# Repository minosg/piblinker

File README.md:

# PiBlinker

A simple python library that provides easy access to to GPIO ports of 20, 21, 26
and enables user to debug behavior on a raspberry pi2 using an RGB led.

It also allows you to attach an ATTINY85 programmed as slave,
if you wish to have external ADC readouts in your project.

Hardware schematics for a simple shield are included, and it costs around 5$ to
manufacture using collaborative panel manufacturers

### Features:
 * Easy to interface logging platform for Raspberry PI boards
 * Easy to manufacture boards even for novice users.
 * Hardware reading of ADC sensor and an extra pin and exposed to the API with
 a file descriptor. No embedded experience required to use, just read/write
 to File.
 * UART/ I2C communication interface, for extra flexibility (i.e Camera Project)
 * Module does not require instantiation, is used directly calling class methods
 * Easy to subclass and create custom routines using decorators
 * Supports already pre-formatted colorized log output with time-stamp and
 optional output to file.
 * Using ANSIColors format that is compatible with Linux, OSX, Putty
 * Log commands also blink the LED to provide an alert system for systems
 running without a screen.
 * Supports different levels of logging with the verbose debugging notifying
 user of the current function and line number in code.
 * Contains simple command line interface for Testing
 * Can be run at background as a well behaved Linux Daemon without super user
 permissions.
 * Daemonized process binds python functions/methods or user defined scripts
 to button events. By default not user set buttons are mapped to Reboot,
 Shutdown.
 * Button binding process can be run at current context, used for debugging or
 with process management scripts such as Supervisord.
 * The library can broadcast strings containing numbers using the LED. This is
 particularly useful in embedded deployment where there is no screen attached
 to the system*.By default it broadcasts the IP aquired  by ```hostname  -I```

_**Each number is represented as a series of blinks,
with the following mapping:*_

 * _*Start digit: Single 1 second Green Pulse*_
 * _*Powers of 100: N 300 mSecond Red Pulses*_
 * _*Powers of 100: N 300 mSecond Green Pulses*_
 * _*Powers of 100: N 300 mSecond Blue Pulses*_
 * _*End of digit: Single 1 Second Red Pulse*_

### Screenshots

#### Console Output

#### PCB

### Installation

Requires http://wiringpi.com/ compiled and installed on the board.
In most distributions this can be done by simply issuing:

`sudo pip install wiringpi2`

Assuming a Raspbian System with python 2.7
```
  cd ~/
  git clone https://github.com/minosg/piblinker.git
  ln -s ~/piblinker /usr/lib/python2.7/dist-packages/piblinker
  # To make the library callable
  ln -s ~/piblinker/piblinker.py /usr/bin/piblinker
```
Ensure you point the symbolic link to the right location.
`locate -b '\dist-packages'` Will help you locate where Python modules
are stored

### Usage

Using the module is as simple as

~~~~~
PiBlinker.setup()

PiBlinker.red("Your text here")
PiBlinker.green("Your text here")
PiBlinker.blue("Your text here")
~~~~~

Setup function also returns a reference to the class object , so you can alias
it:

~~~~~
pilogger = PiBlinker.setup()

pilogger.info("Your text here")
pilogger.warning("Your text here")
pilogger.error("Your text here")
pilogger.debug("Your text here")
~~~~~

### Further customization
If you are unhappy with the default configuration you can specify parameters in
the setup function:

~~~~~
PiBlinker.setup(log_level, log_label, log_path, log_colors)
~~~~~

#### log_label
Is just the name you want to assign to the logger. It is included in every line
of log produced. The recommended standard is to set it to the __file__ name.

#### log_level
The standard level of logging. Piblinker will ignore all logging commands that
are above the current level. Supported levels are :

* info
* warning
* error
* debug
* ver_debug

Setting level to info will only display and write to file info calls, while
setting debug will print everything. Verbose debug is a special debug level that
also inspects the function  that called it and displays the information to
screen. In every other aspect ver_debug is identical to debug.

#### log_path
The file that the logging commands will be saved to.Not setting a path will only
display commands and blink the LED.

#### log_colors
This parameter allows you to override the default colors that will be displayed
by the logger to screen.It DOES not affect the blinking led behavior. Input will
be sanitized and if you attempt to set an invalid level or invalid color, it
will be ignored

~~~~~
llevels = {"info": "CYAN",
           "warning":"UBLUE",
           "error": "HRED",
           "ver_debug": "WHITE"}
~~~~~

Note that prefixing a color adjusts the formatting:
 * U  -> underline
 * H  -> Highlight
 * UH -> Underline && Highlight

### Communicating with ATTINY85

#### i2c

The file descriptors can be accessed using

~~~~~
readf, writef = PiBlinker.i2c_open_file(0x04, 1)
... do stuff
PiBlinker.i2c_close(0x04)
~~~~~

There are interface commands some simple readouts

~~~~~
adc_val = PiBlinker.i2c_read_adc(0x04)
chip_in = PiBlinker.i2c_read_pin(0x04)
~~~~~

#### UART

~~~~~
PiBlinker.uart_open()
print "ADC:", PiBlinker.uart_read("ADC")
print "PIN:", PiBlinker.uart_read("PIN")
PiBlinker.uart_close()
~~~~~

#### Switching between UART and I2C communications

By default the ATTINY85 will boot in UART mode, poll the port for a short time
interval waiting for a special byte and fall-back to use i2c interface (default)
if nothing is received. If the byte is received, then it will set UART mode as
default.

This behavior can be tested using ```piblinker -a``` , but when using the
library in custom projects, which may power cycle ensure that

~~~~~~
PiBlinker.uart_activate()
~~~~~~
 is run at power-up

### Supported Test commands

~~~~~
piblinker -t all: Test i2c communications and led
piblinker -t led: Test led
piblinker -t log: Test led and loging output
piblinker -t i2c: Test i2c comms
piblinker -t poll: Continously poll ADC Switch readouts
piblinker -t uart: Get serial readouts
piblinker -a: Activate UART mode after a reset
~~~~~

### Extra Features

To make the module broadcast the IP address using the LED use
~~~~~
piblinker -t
~~~~~

To run the button monitor daemon a set of optional arguments are supported
~~~~~
piblinker -d
piblinker -d -b1 /home/yourscript.sh -b2 /usr/bin/ls
piblinker -d -b1 /home/yourscript.sh -u someuser
piblinker -d -b1 /home/yourscript.sh -u someuser -s letmein
~~~~~

Argument ```-d --daemon``` runs the button watchdog as a daemon.
If that is not the desired behavior it can replaced by ```-nd --nodaemon```

Arguments ```-bX``` indicate the button that you wish to bind the script.The
library at current state only supports two buttons but can be easily modified
to extend that functionality. If a script is not set the default behavior is
to bind one button to shutdown and one to reboot. When called from python code,
those arguments are method pointers so perform any task.

By default the library **assumes** that the user has elevated permission to
execute task set in the /etc/sudoers with the NOPASSWORD directive i.e

~~~~~~
limited_user     ALL=NOPASSWD: /sbin/reboot
or (non recommended)
ALL     ALL=NOPASSWD: /sbin/reboot
~~~~~~

By default triggered command will be executed using sudo. If that is not the
case the ```-s``` directive is needed to let the library fill the sudo password.

In some occasions the script needs to be run as a different user. Using ```-u```
in combination with a valid sudo password for the user running the daemon, **not
the target user who will execute the command**, is recommended.

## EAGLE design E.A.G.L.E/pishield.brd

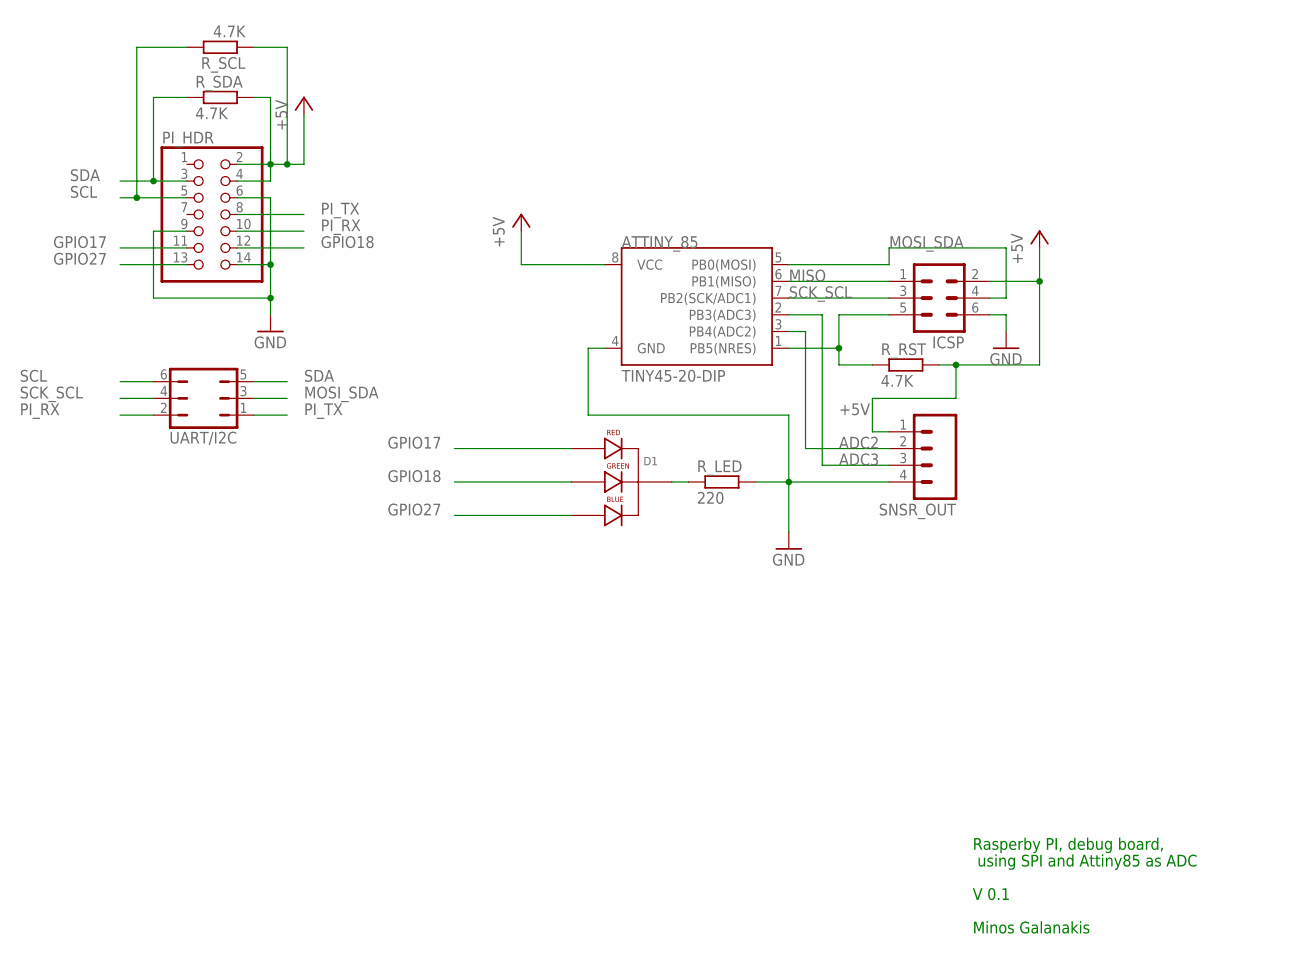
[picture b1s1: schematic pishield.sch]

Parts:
ATTINY_85: TINY45-20-DIP; DIP08
D1: LED-RGB-CC-THRUCLEAR; LED-RGB-THRU
ICSP: MA03-2
PI_HDR: PINHD-2X7; 2X07
R_LED: 220; 0204/7
R_RST: 4.7K; 0204/7
R_SCL: 4.7K; 0204/7
R_SDA: 4.7K; 0204/7
SNSR_OUT: M04LONGPADS; 1X04_LONGPADS
UART/I2C: JP3Q

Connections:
+5V: ATTINY_85.8 (VCC), ICSP.2, PI_HDR.2, PI_HDR.4, R_RST.2, R_SCL.1, R_SDA.2, SNSR_OUT.1
ADC2: ATTINY_85.3 (PB4(ADC2)), SNSR_OUT.2
ADC3: ATTINY_85.2 (PB3(ADC3)), SNSR_OUT.3
GND: ATTINY_85.4 (GND), ICSP.6, PI_HDR.6, PI_HDR.9, PI_HDR.14, R_LED.2, SNSR_OUT.4
GPIO17: D1.1 (RED_CATHODE), PI_HDR.11
GPIO18: D1.3 (GREEN_CATHODE), PI_HDR.12
GPIO27: D1.4 (BLUE_CATHODE), PI_HDR.13
MISO: ATTINY_85.6 (PB1(MISO)), ICSP.1
MOSI_SDA: ATTINY_85.5 (PB0(MOSI)), ICSP.4, UART/I2C.3
unnamed: D1.2 (CATHODE), R_LED.1
unnamed: ATTINY_85.1 (PB5(NRES)), ICSP.5, R_RST.1
PI_RX: PI_HDR.10, UART/I2C.2
PI_TX: PI_HDR.8, UART/I2C.1
SCK_SCL: ATTINY_85.7 (PB2(SCK/ADC1)), ICSP.3, UART/I2C.4
SCL: PI_HDR.5, R_SCL.2, UART/I2C.6
SDA: PI_HDR.3, R_SDA.1, UART/I2C.5

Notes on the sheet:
Rasperby PI, debug board,
using SPI and Attiny85 as ADC
V 0.1
Minos Galanakis

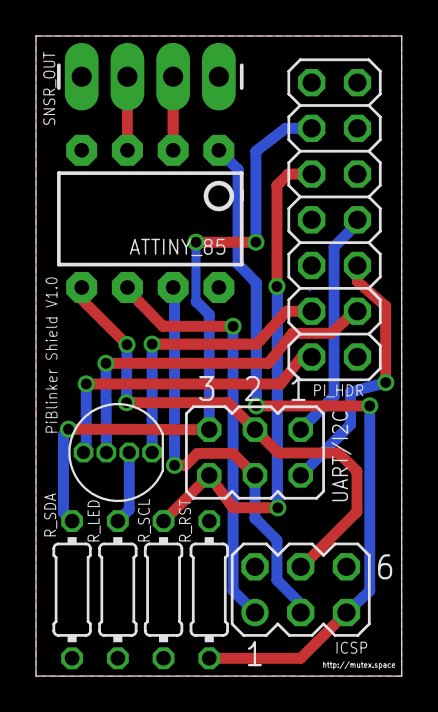
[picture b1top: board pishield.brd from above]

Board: 2 copper layers, 20.3 x 35.6 mm, 10 parts (0 on the bottom side), 16 nets.

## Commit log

2015-06-01 Init commit
2015-06-01 piblinker.py: First implementation of pi blinker, only supports 3 colors
2015-06-25 piblinker.py: Functionality updated to include raw i2c communication
2015-06-26 piblinker.py: Added alias i2c_read_adc command
2015-06-26 attiny85: Added basic ADC slave support from Attiny85 chip using tinywire library
2015-07-07 piblinker.py: Updated pin configurations for the piblinker shield
2015-07-08 piblinker.py: Added command line tests
2015-07-08 attiny_dual_uart.ino: Added arduino code for Serial operation
2015-07-09 piblinker.py: Added support for multiplexed dual reading, updated arduino code accordingly
2015-07-09 Added dual mode operation firmware for Attiny, that automatically swicthes from UART to I2C
2015-07-09 piblinker.py: Added UART mode support and test/activate cases
2015-10-05 Added test hardware routine, refined error handling when failing to open I2C socket
2015-10-06 Added hardware schematics for the PiBlinker Shield
2016-03-16 Decorated led_print routines
2016-03-17 Added colorlogging module, modified led_blink to utilize decorators
2016-03-18 Added support for complex LED colors
2016-03-21 pidaemon: Added new module that daemonizes the library
2016-03-23 piblinker: Added argparser module, led_bcast function, non daemon monitor start

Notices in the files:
parts and their libraries:
SparkFun-DigitalIC: Licensing: Creative Commons ShareAlike 4.0 International - https://creativecommons.org/licenses/by-sa/4.0
